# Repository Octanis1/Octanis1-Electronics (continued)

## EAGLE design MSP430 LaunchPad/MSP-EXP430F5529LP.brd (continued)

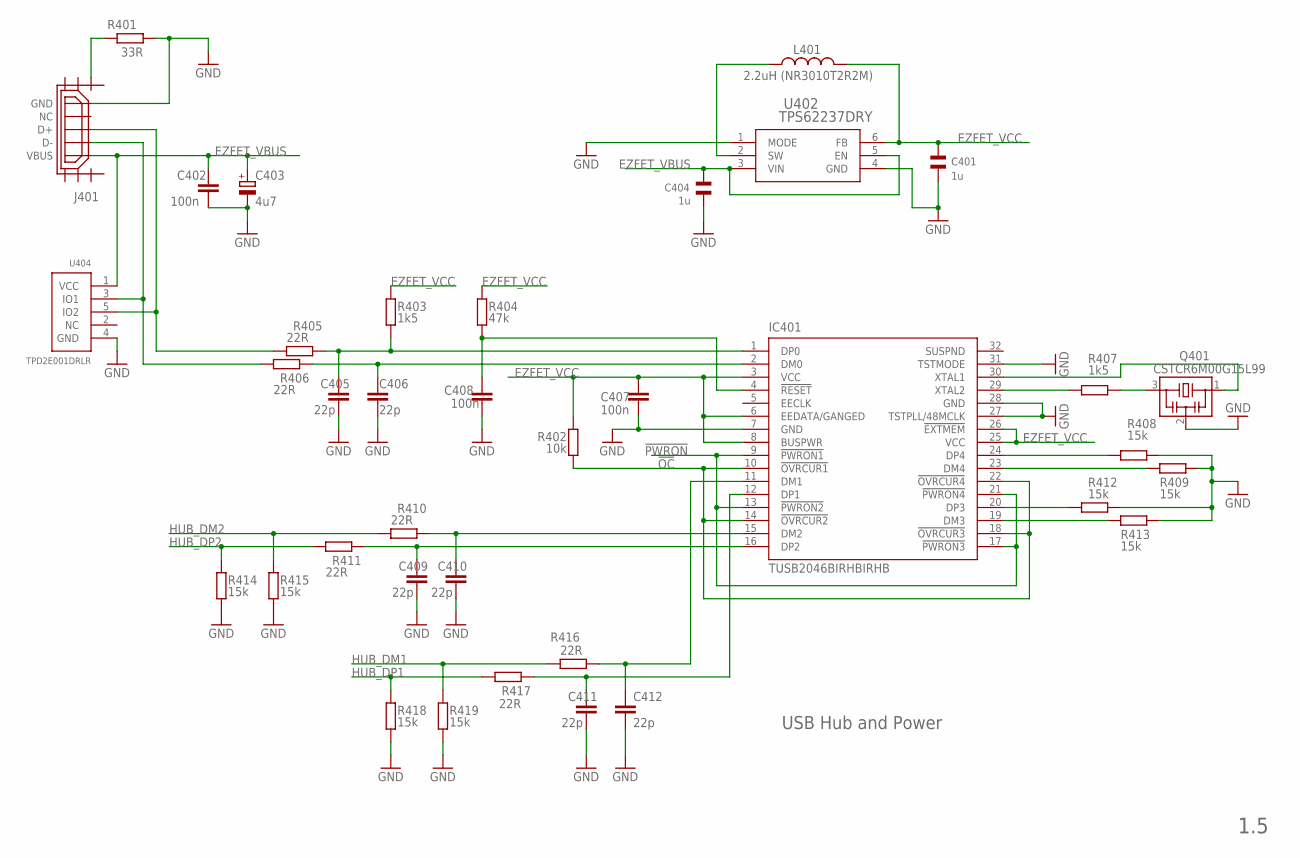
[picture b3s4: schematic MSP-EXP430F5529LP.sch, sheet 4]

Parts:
C401, C404: 1u; CSMD0805
C402, C407, C408: 100n; C0402
C403: 4u7; A/3216-18R
C405, C406, C409, C410, C411, C412: 22p; C0402
IC401: TUSB2046BIRHBIRHB; RHB_S-PQFP-N32
J401: USB_MICRO_FLIPPED; HIROSE-ZX62R-B-5P
L401: 2.2uH (NR3010T2R2M); L-NR3010
Q401: CSTCR6M00G15L99; MURATA-FILTER_CSTCR
R401: 33R; R0402
R402: 10k; R0402
R403, R407: 1k5; R0402
R404: 47k; R0402
R405, R406, R410, R411, R416, R417: 22R; R0402
R408, R409, R412, R413, R414, R415, R418, R419: 15k; R0402
U402: TPS62237DRY; DRY6
U404: TPD2E001DRLR; TPD2E001-DRL

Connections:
!OC: IC401.10 (!OVRCUR1), IC401.14 (!OVRCUR2), IC401.18 (!OVRCUR3), IC401.22 (!OVRCUR4), R402.2
!PWRON: IC401.9 (!PWRON1), IC401.13 (!PWRON2), IC401.17 (!PWRON3), IC401.21 (!PWRON4)
EZFET_VBUS: C402.1, C403.+, C404.2, J401.VBUS, U402.3 (VIN), U402.5 (EN), U404.1 (VCC); also elsewhere on the board
EZFET_VCC: C401.2, C407.1, IC401.3 (VCC), IC401.6 (EEDATA/GANGED), IC401.8 (BUSPWR), IC401.25 (VCC), IC401.26 (!EXTMEM), L401.P$2 (2), R402.1, R403.1, R404.1, U402.6 (FB); also elsewhere on the board
GND: C401.1, C402.2, C403.-, C404.1, C405.2, C406.2, C407.2, C408.2, C409.2, C410.2, C411.2, C412.2, IC401.7 (GND), IC401.27 (TSTPLL/48MCLK), IC401.28 (GND), IC401.31 (TSTMODE), J401.GND, Q401.2, R401.2, R408.1, R409.1, R412.1, R413.1, R414.2, R415.2, R418.2, R419.2, U402.1 (MODE), U402.4 (GND), U404.4 (GND); also elsewhere on the board
HUB_DM1: R416.2, R419.1; also elsewhere on the board
HUB_DM2: R410.2, R415.1; also elsewhere on the board
HUB_DP1: R417.2, R418.1; also elsewhere on the board
HUB_DP2: R411.2, R414.1; also elsewhere on the board
unnamed: C410.1, IC401.15 (DM2), R410.1
unnamed: C405.1, IC401.1 (DP0), R403.2, R405.1
unnamed: IC401.30 (XTAL1), Q401.1
unnamed: J401.SHIELD1, R401.1
unnamed: C406.1, IC401.2 (DM0), R406.1
unnamed: J401.D+, R405.2, U404.5 (IO2)
unnamed: J401.D-, R406.2, U404.3 (IO1)
unnamed: L401.P$1 (1), U402.2 (SW)
unnamed: IC401.29 (XTAL2), R407.2
unnamed: C412.1, IC401.11 (DM1), R416.1
unnamed: C411.1, IC401.12 (DP1), R417.1
unnamed: C409.1, IC401.16 (DP2), R411.1
unnamed: C408.1, IC401.4 (!RESET), R404.2
unnamed: IC401.20 (DP3), R412.2
unnamed: IC401.24 (DP4), R408.2
unnamed: IC401.23 (DM4), R409.2
unnamed: IC401.19 (DM3), R413.2
unnamed: Q401.3, R407.1

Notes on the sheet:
USB Hub and Power
1.5

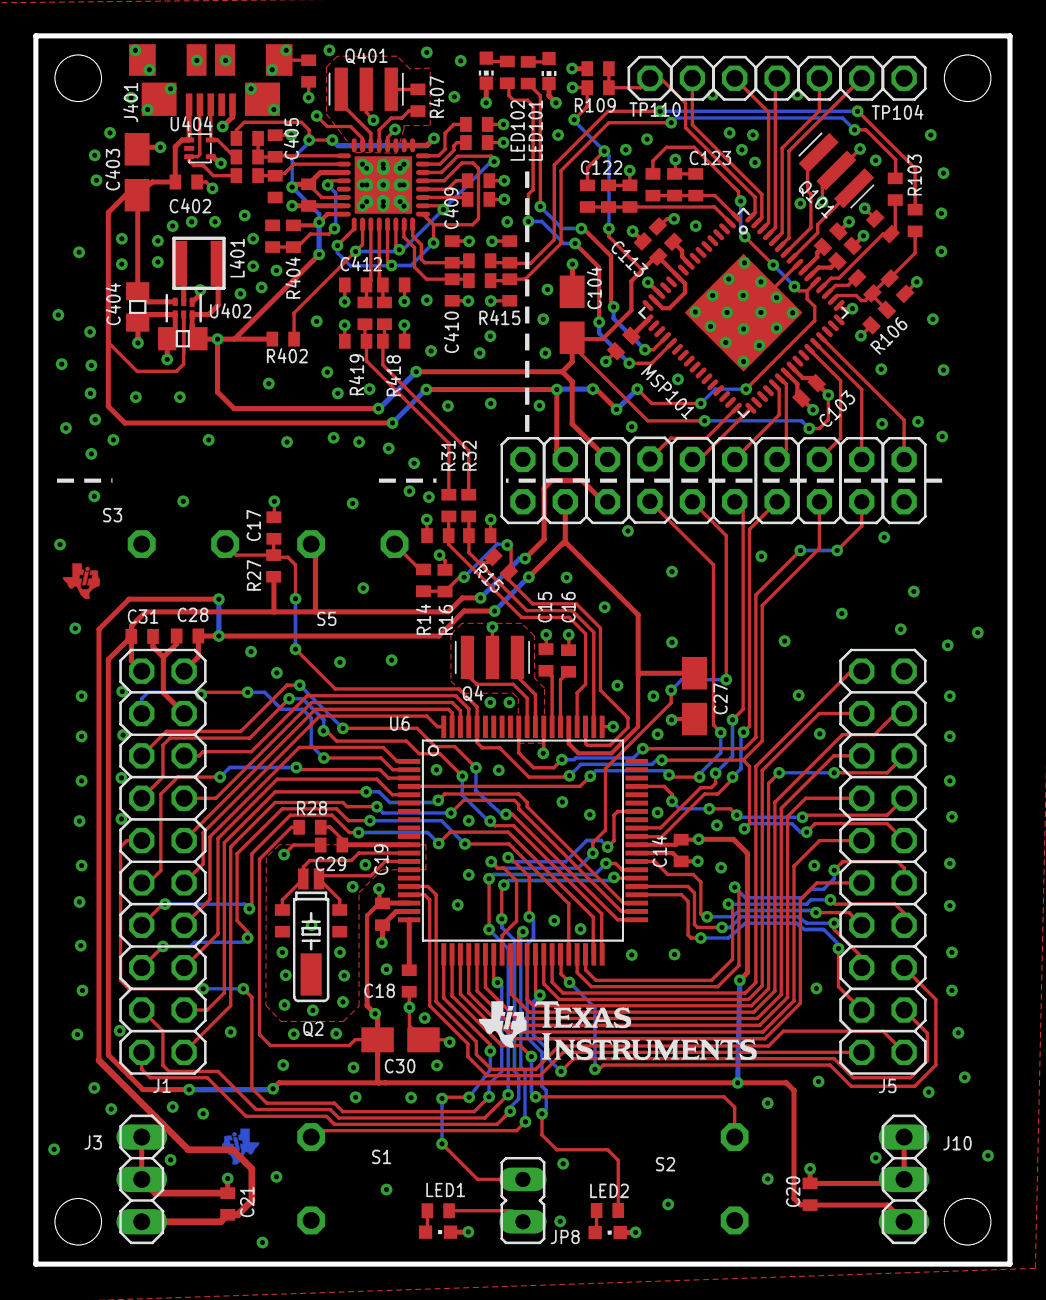
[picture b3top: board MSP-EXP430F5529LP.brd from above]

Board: 2 copper layers, 58.4 x 73.7 mm, 132 parts (1 on the bottom side), 117 nets.

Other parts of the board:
DRAW2: LOGO-ROCKET-10X7MM-BRD
U$1: LOGO16_TPLACE
U$2, U$5: TILOGO_SMALL

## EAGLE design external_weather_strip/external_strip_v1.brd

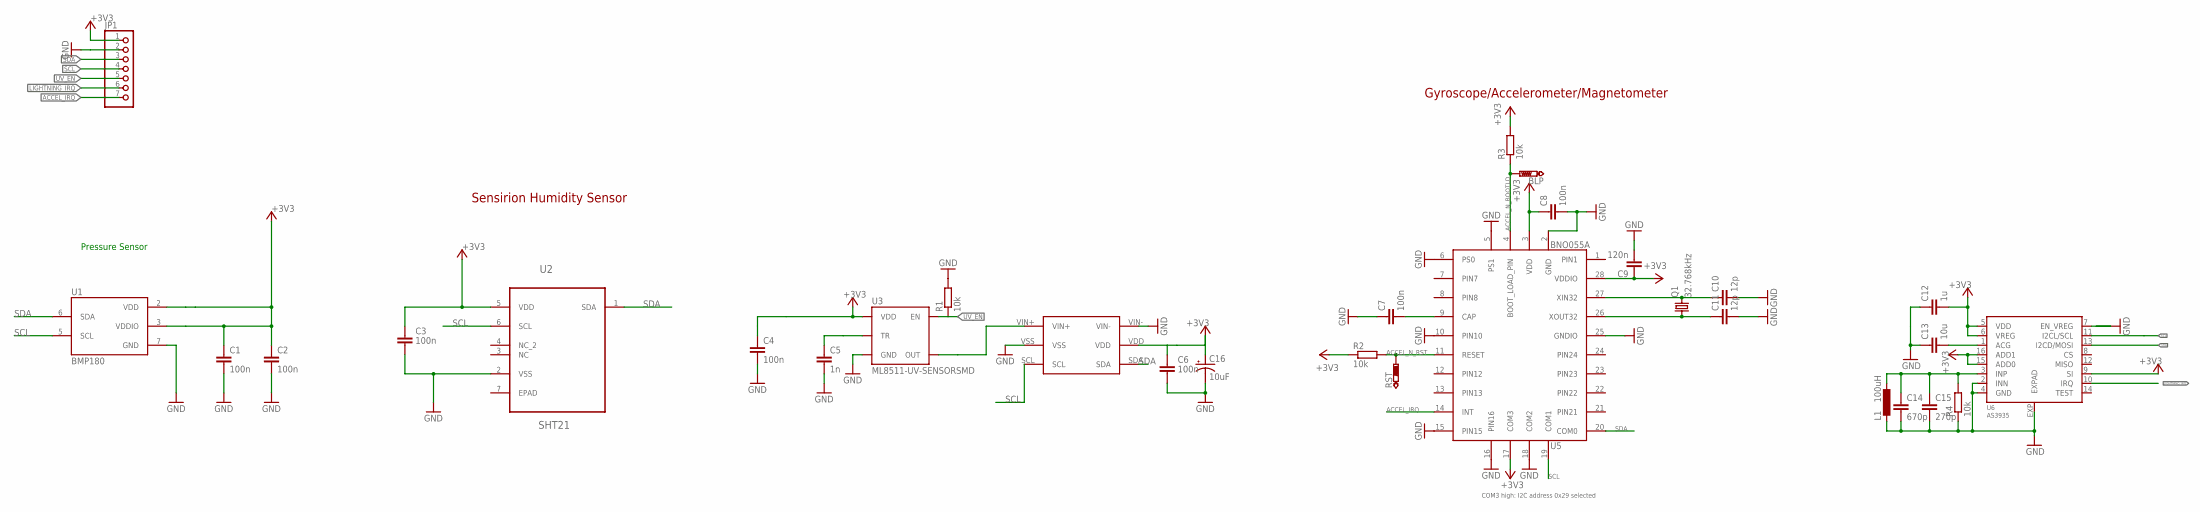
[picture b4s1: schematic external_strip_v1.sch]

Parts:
BLP: PTR1B1,27; B1,27
C1, C2, C3, C6, C7, C8: 100n; C0603
C4: 100n; 0603-CAP
C5: 1n; 0603-CAP
C9: 120n; C0603
C10, C11: 12p; C0603
C12: 1u; C0603
C13: 10u; C0603
C14: 670p; C0603
C15: 270p; C0603
C16: 10uF; EIA3216
JP1: PINHD-1X7; 1X07
L1: 100uH; COILCRAFT
Q1: 32.768kHz; FC-12M
R1, R2, R3, R4: 10k; R0603
RST: PTR1B1,27; B1,27
U1: BMP180
U2: SHT21; DFN300X300X110-7N
U3: ML8511-UV-SENSORSMD; ML8511
U4: MCP3425; SOT-23-6
U5: BNO055A; BNO055
U6: AS3935; 16LDMLPQ

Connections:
+3V3: C1.1, C2.1, C3.1, C4.1, C6.1, C8.1, C9.1, C12.2, C16.A (+), JP1.1, R2.1, R3.2, U1.2 (VDD), U1.3 (VDDIO), U2.5 (VDD), U3.7 (VDD), U4.VDD, U5.3 (VDD), U5.17 (COM3), U5.28 (VDDIO), U6.5 (VDD), U6.6 (VREG), U6.9 (SI), U6.15 (ADD0), U6.16 (ADD1)
ACCEL_IRQ: JP1.7, U5.14 (INT)
ACCEL_N_BOOTLD: BLP.TP, R3.1, U5.4 (BOOT_LOAD_PIN)
ACCEL_N_RST: R2.2, RST.TP, U5.11 (RESET)
GND: C1.2, C2.2, C3.2, C4.2, C5.2, C6.2, C7.1, C8.2, C9.2, C10.2, C11.2, C12.1, C13.1, C14.2, C15.2, C16.C (-), JP1.2, L1.2, R1.2, R4.1, U1.7 (GND), U2.2 (VSS), U3.5 (GND), U4.VIN-, U4.VSS, U5.2 (GND), U5.5 (PS1), U5.6 (PS0), U5.10 (PIN10), U5.15 (PIN15), U5.16 (PIN16), U5.18 (COM2), U5.25 (GNDIO), U6.2 (INN), U6.4 (GND), U6.7 (EN_VREG), U6.EXP (EXPAD)
LIGHTNING_IRQ: JP1.6, U6.10 (IRQ)
unnamed: U3.8 (OUT), U4.VIN+
unnamed: C13.2, U6.1 (ACG)
unnamed: C5.1, U3.10 (TR)
unnamed: C14.1, C15.1, L1.1, R4.2, U6.3 (INP)
unnamed: C7.2, U5.9 (CAP)
unnamed: C10.1, Q1.2, U5.27 (XIN32)
unnamed: C11.1, Q1.1, U5.26 (XOUT32)
SCL: JP1.4, U1.5 (SCL), U2.6 (SCL), U4.SCL, U5.19 (COM1), U6.11 (I2CL/SCL)
SDA: JP1.3, U1.6 (SDA), U2.1 (SDA), U4.SDA, U5.20 (COM0), U6.13 (I2CD/MOSI)
UV_EN: JP1.5, R1.1, U3.4 (EN)

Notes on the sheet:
Sensirion Humidity Sensor
Pressure Sensor
Gyroscope/Accelerometer/Magnetometer
COM3 high: I2C address 0x29 selected

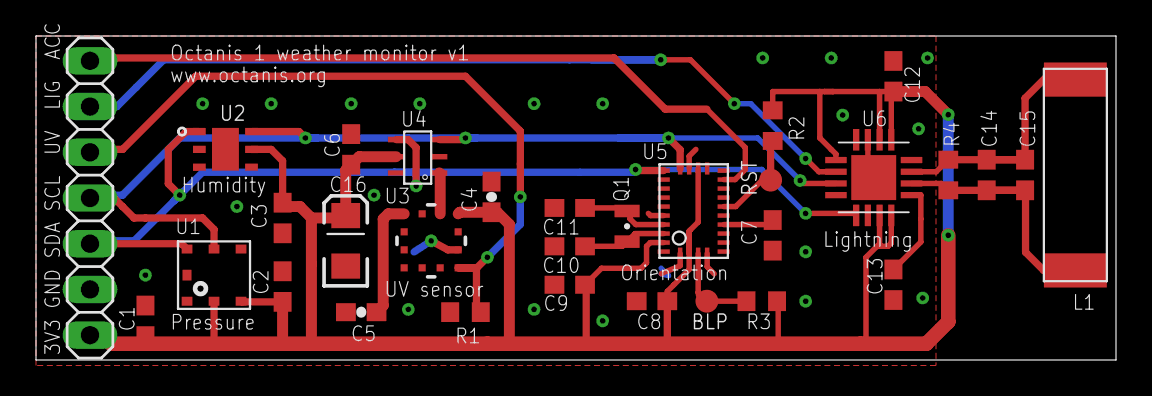
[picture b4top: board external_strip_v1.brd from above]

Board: 2 copper layers, 60.0 x 18.0 mm, 31 parts (0 on the bottom side), 16 nets.

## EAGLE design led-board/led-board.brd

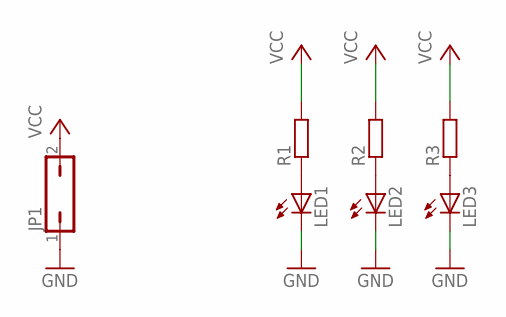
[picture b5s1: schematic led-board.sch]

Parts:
JP1: JP1Q; JP1
LED1, LED2, LED3: LED5MM
R1, R2, R3: R-EU_0414/15; 0414/15

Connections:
GND: JP1.1, LED1.K (C), LED2.K (C), LED3.K (C)
unnamed: LED1.A, R1.1
unnamed: LED2.A, R2.1
unnamed: LED3.A, R3.1
VCC: JP1.2, R1.2, R2.2, R3.2

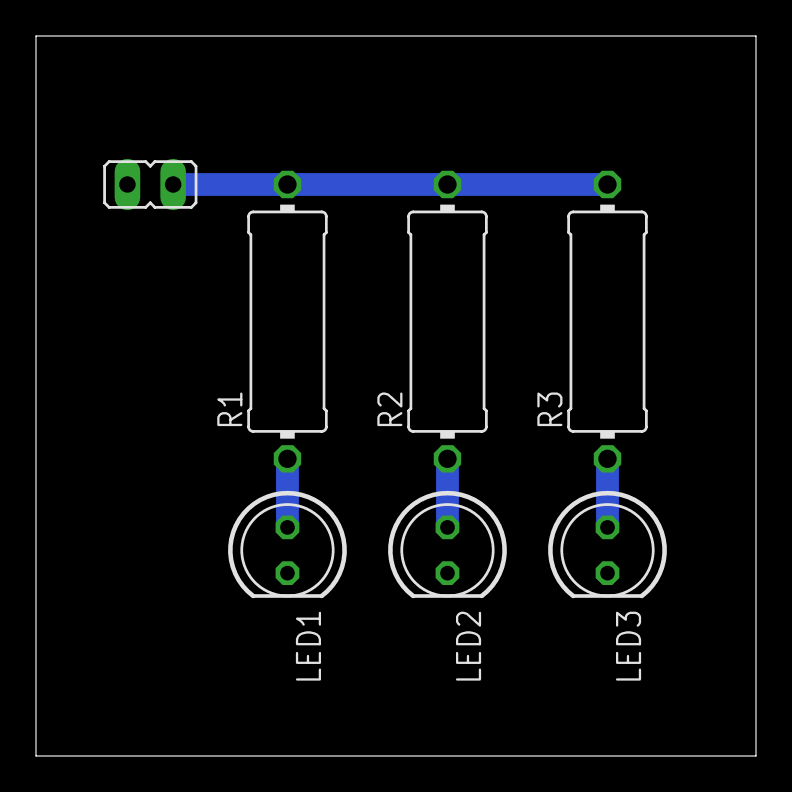
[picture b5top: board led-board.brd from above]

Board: 2 copper layers, 40.0 x 40.0 mm, 7 parts (0 on the bottom side), 5 nets.

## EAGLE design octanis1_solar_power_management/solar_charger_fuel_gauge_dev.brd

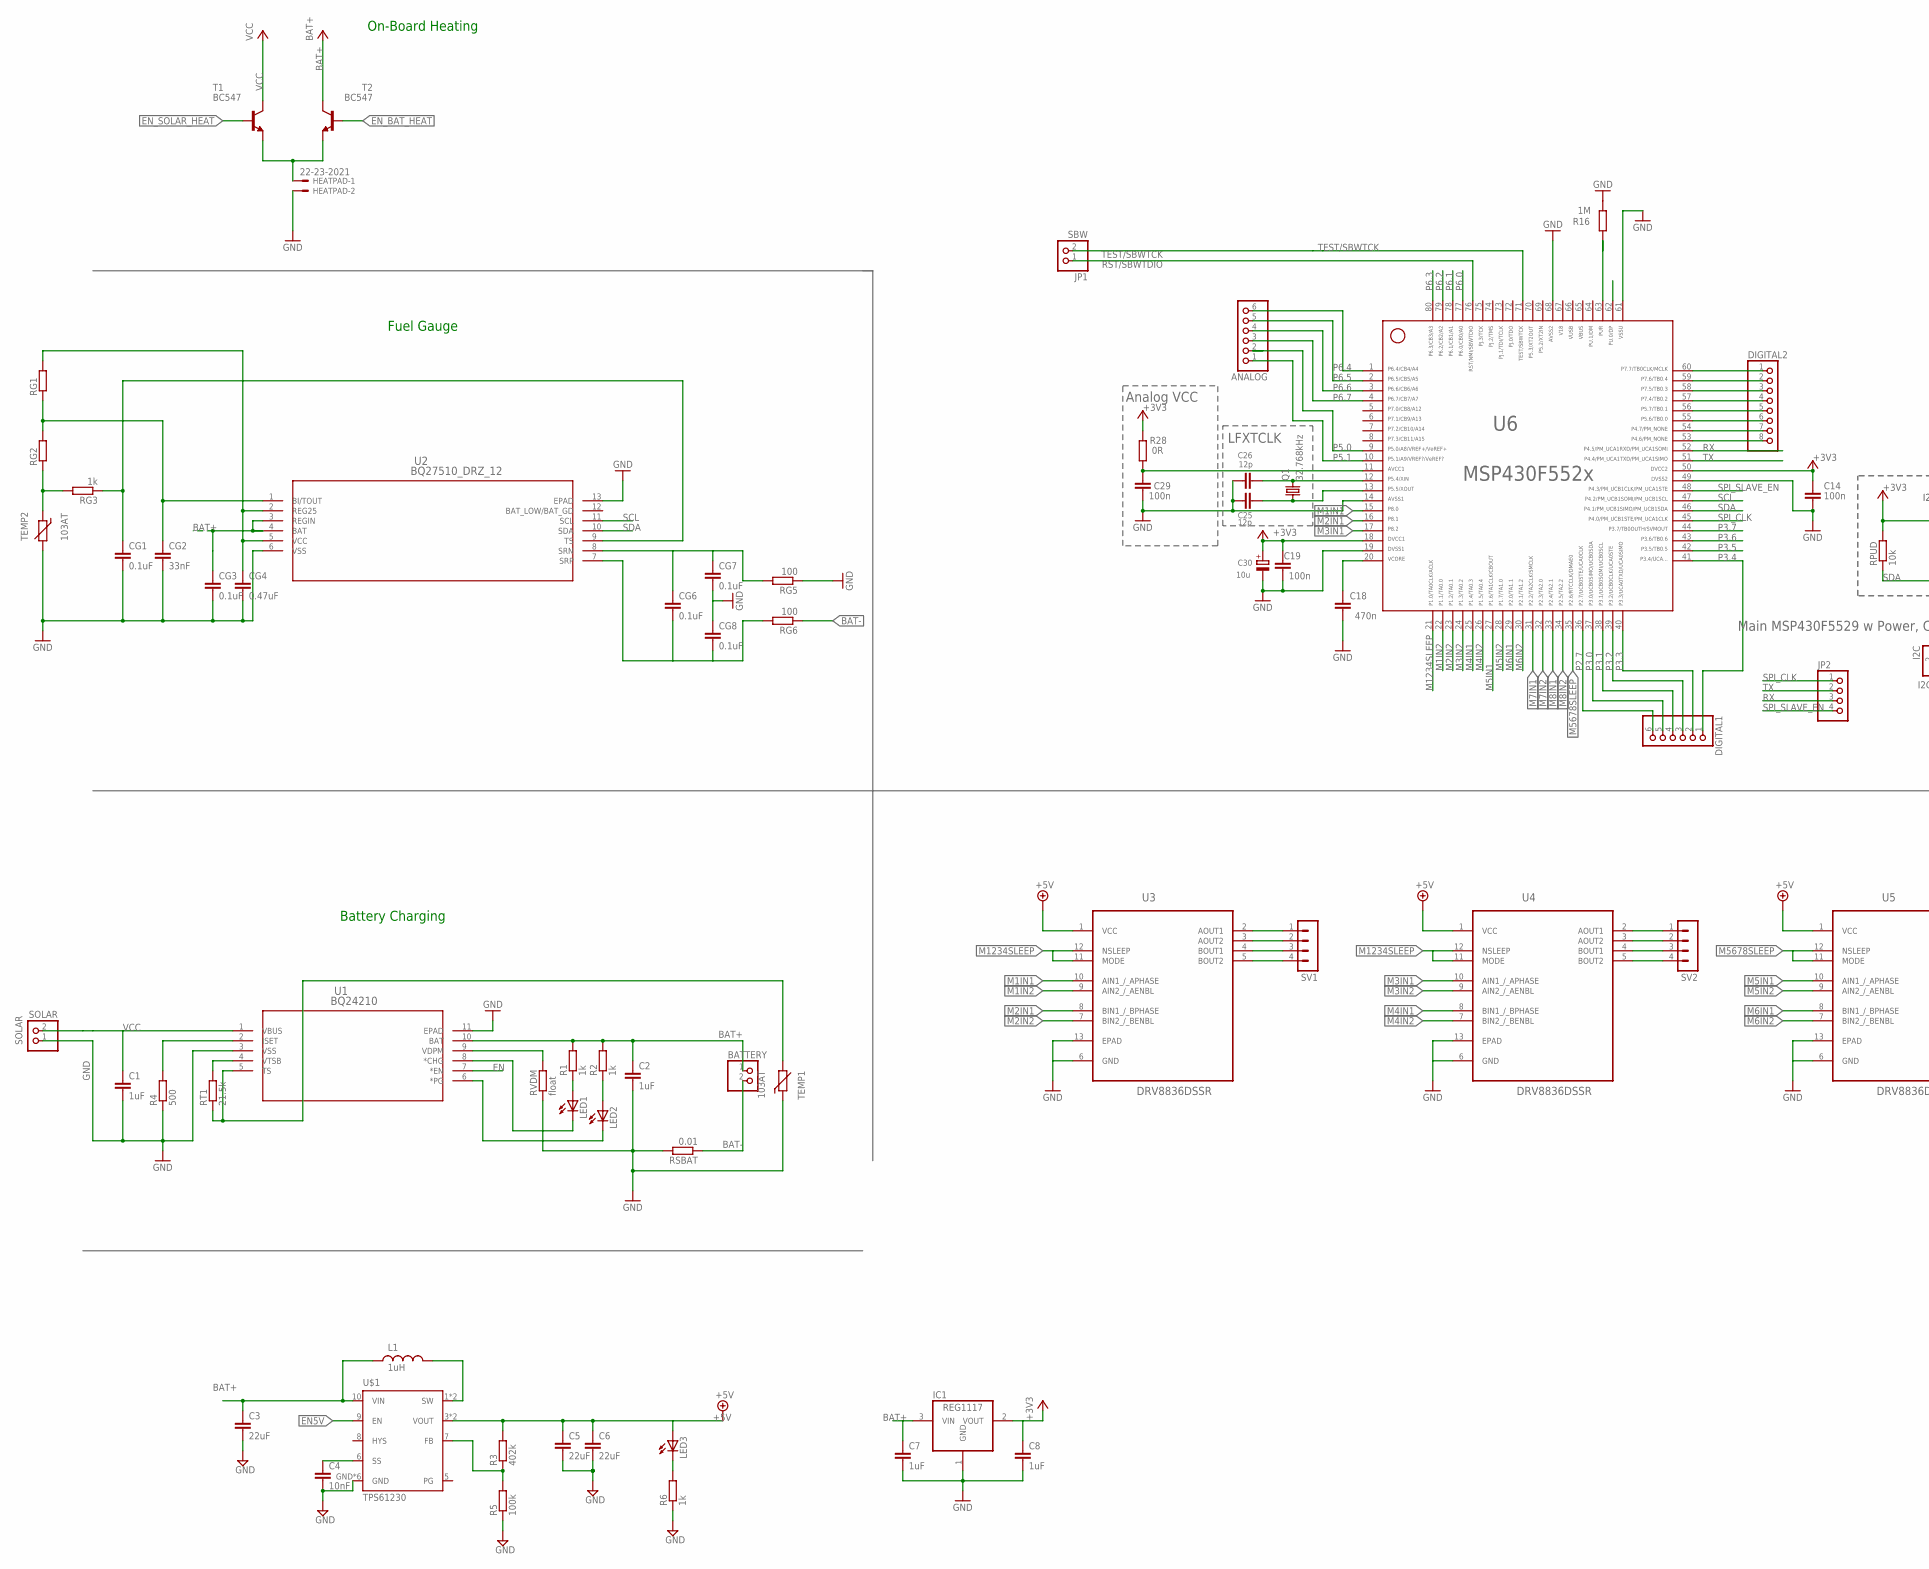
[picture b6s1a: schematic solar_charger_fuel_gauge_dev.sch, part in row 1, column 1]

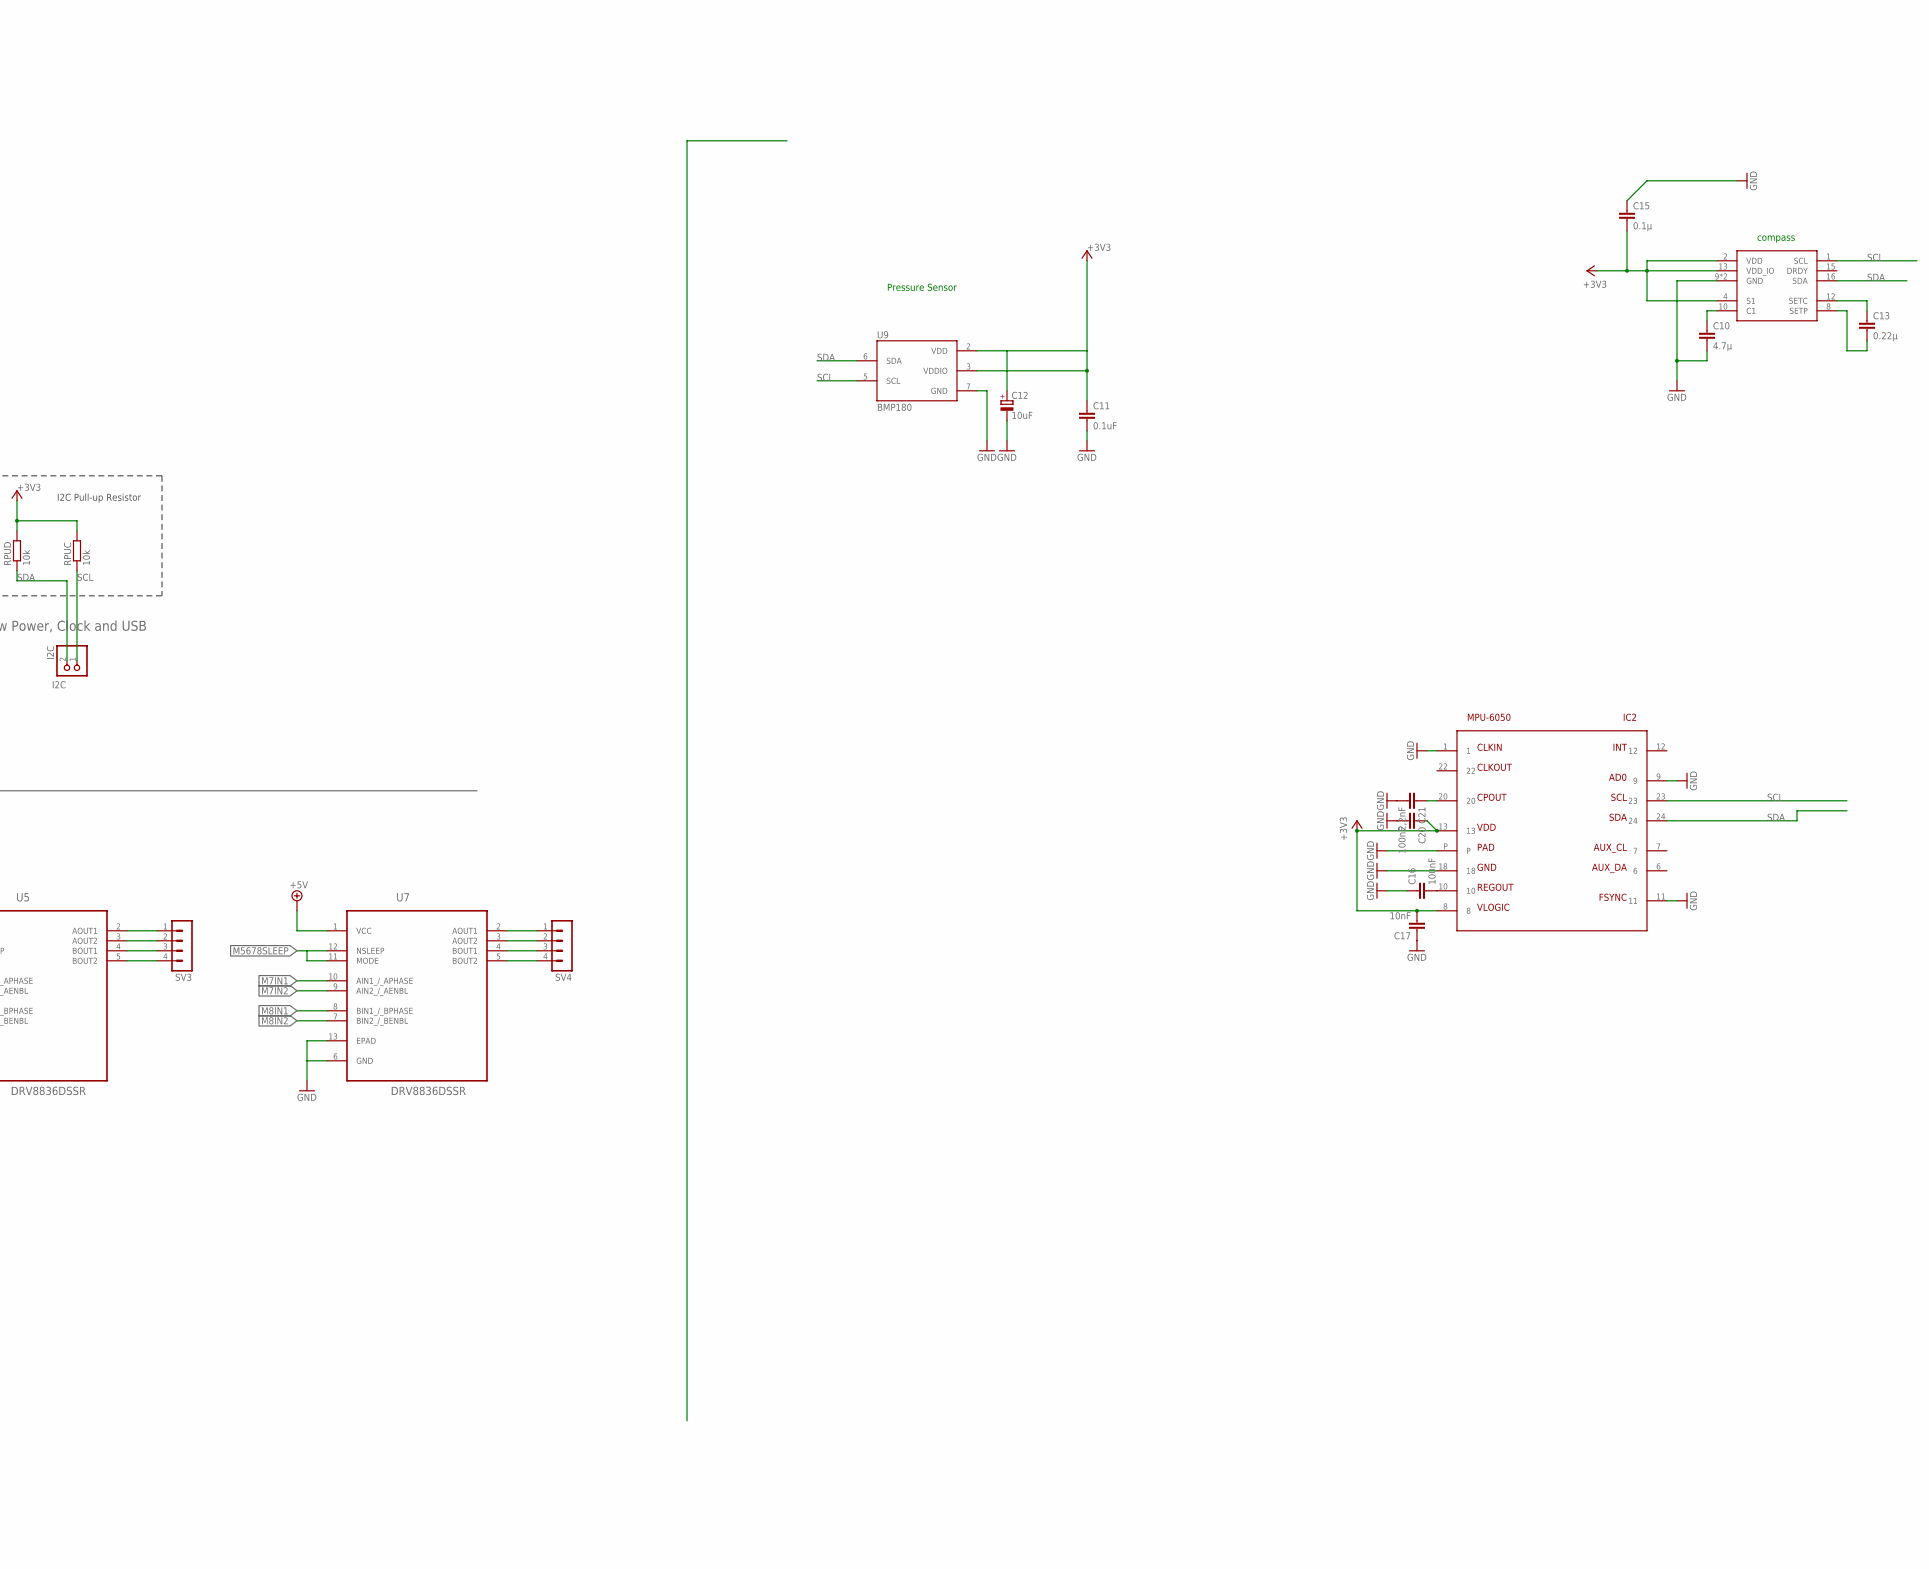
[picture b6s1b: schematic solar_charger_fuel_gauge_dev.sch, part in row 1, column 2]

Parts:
ANALOG: PINHD-1X6; 1X06
BATTERY: PINHD-1X2; 1X02
C1, C2: 1uF; C1206
C3, C5, C6: 22uF; C0603
C4, C17: 10nF; C0603
C7, C8: 1uF; C0603
C10: 4.7µ; C0603
C11: 0.1uF; C0603
C12: 10uF; A/3216-18R
C13: 0.22µ; C0603
C14, C19, C29: 100n; C0603
C15: 0.1µ; C0603
C16, C20: 100nF; C0603
C18: 470n; C0603
C21: 2,2nF; C0603
C25, C26: 12p; C0603
C30: 10u; A/3216-18R
CG1, CG3, CG6, CG7, CG8: 0.1uF; C0603
CG2: 33nF; C0603
CG4: 0.47uF; C0603
COMPASS: HMC5883L; LPCC16
DIGITAL1: PINHD-1X6; 1X06
DIGITAL2: PINHD-1X8; 1X08
HEATPAD: 22-23-2021
I2C: I2C; 1X02
IC1: REG1117; SOT223
IC2: MPU-6050; QFN24
JP1: SBW; 1X02
JP2: PINHD-1X4; 1X04
L1: 1uH; XFL4020
LED1, LED2: LEDCHIP-LED0603; CHIP-LED0603
LED3: LEDCHIPLED_0603; CHIPLED_0603
Q1: 32.768kHz; FC-12M
R1, R2, R6: 1k; R0603
R3: 402k; R0603
R4: 500; R1206
R5: 100k; R0603
R16: 1M; R0603
R28: 0R; R0603
RG1, RG2: R-EU_R0603; R0603
RG3: 1k; R0603
RG5, RG6: 100; R0603
RPUC: 10k; R0603
RPUD: 10k; R0603
RSBAT: 0.01; R1206
RT1: 21.5k; R1206
RVDM: float; R1206
SOLAR: SOLAR; 1X02
SV1, SV2, SV3, SV4: MA04-1
T1, T2: BC547; TO92
TEMP1, TEMP2: 103AT; RS-2,5
U1: BQ24210; DQC10_P84X2P4
U2: BQ27510_DRZ_12; DRZ12_1P95X2P45
U3, U4, U5, U7: DRV8836DSSR; SON50P200X300X80-13N
U6: MSP430F5529IPNR; PN80
U9: BMP180
U$1: TPS61230; DRC-S-PVSON-N11

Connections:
65: U6.65
66: U6.66
67: U6.67
+3V3: C8.1, C11.1, C12.+, C14.1, C15.2, C17.2, C19.2, C20.1, C30.+, COMPASS.2 (VDD), COMPASS.4 (S1), COMPASS.13 (VDD_IO), IC1.2 (VOUT), IC2.8, IC2.13, R28.2, RPUC.2, RPUD.2, U6.18, U6.50, U9.2 (VDD), U9.3 (VDDIO)
+5V: C5.1, C6.1, LED3.A, R3.2, U3.1 (VCC), U4.1 (VCC), U5.1 (VCC), U7.1 (VCC), U$1.3 (VOUT), U$1.4 (VOUT)
AVCC: C29.1, R28.1, U6.11
BAT+: BATTERY.1, C2.1, C3.1, C7.1, CG3.1, IC1.3 (VIN), L1.P$1 (1), R1.2, R2.2, T2.3 (C), U1.10 (BAT), U2.3 (REGIN), U2.4 (BAT), U$1.10 (VIN)
BAT-: BATTERY.2, RG6.1, RSBAT.1
EN: U1.7 (*EN)
EN5V: U$1.9 (EN)
EN_BAT_HEAT: T2.2 (B)
EN_SOLAR_HEAT: T1.2 (B)
GND: C1.2, C2.2, C3.2, C4.2, C5.2, C6.2, C7.2, C8.2, C10.2, C11.2, C12.-, C14.2, C15.1, C16.1, C17.1, C18.1, C19.1, C20.2, C21.2, C25.1, C26.1, C29.2, C30.-, CG1.2, CG2.2, CG3.2, CG4.2, CG7.2, CG8.1, COMPASS.9 (GND), COMPASS.11 (GND), HEATPAD.2, IC1.1 (GND), IC2.1, IC2.9, IC2.11, IC2.18, IC2.P, R4.1, R5.1, R6.1, R16.1, RG5.1, RSBAT.2, RVDM.1, SOLAR.1, TEMP1.1, TEMP2.2, U1.3 (VSS), U1.11 (EPAD), U2.6 (VSS), U2.13 (EPAD), U3.6 (GND), U3.13 (EPAD), U4.6 (GND), U4.13 (EPAD), U5.6 (GND), U5.13 (EPAD), U6.14, U6.19, U6.49, U6.61, U6.68, U7.6 (GND), U7.13 (EPAD), U9.7 (GND), U$1.GND, U$1.GND@1 (GND), U$1.GND@2 (GND), U$1.GND@3 (GND), U$1.GND@4 (GND), U$1.GND@5 (GND)
IND: L1.P$2 (2), U$1.1 (SW), U$1.2 (SW)
M1IN1: U3.10 (AIN1_/_APHASE), U6.15
M1IN2: U3.9 (AIN2_/_AENBL), U6.22
M2IN1: U3.8 (BIN1_/_BPHASE), U6.16
M2IN2: U3.7 (BIN2_/_BENBL), U6.23
M3IN1: U4.10 (AIN1_/_APHASE), U6.17
M3IN2: U4.9 (AIN2_/_AENBL), U6.24
M4IN1: U4.8 (BIN1_/_BPHASE), U6.25
M4IN2: U4.7 (BIN2_/_BENBL), U6.26
M5IN1: U5.10 (AIN1_/_APHASE), U6.27
M5IN2: U5.9 (AIN2_/_AENBL), U6.28
M6IN1: U5.8 (BIN1_/_BPHASE), U6.29
M6IN2: U5.7 (BIN2_/_BENBL), U6.30
M7IN1: U6.31, U7.10 (AIN1_/_APHASE)
M7IN2: U6.32, U7.9 (AIN2_/_AENBL)
M8IN1: U6.33, U7.8 (BIN1_/_BPHASE)
M8IN2: U6.34, U7.7 (BIN2_/_BENBL)
M1234SLEEP: U3.11 (MODE), U3.12 (NSLEEP), U4.11 (MODE), U4.12 (NSLEEP), U6.21
M5678SLEEP: U5.11 (MODE), U5.12 (NSLEEP), U6.35, U7.11 (MODE), U7.12 (NSLEEP)
unnamed: CG2.1, RG1.1, RG2.2, U2.1 (BI/TOUT)
unnamed: LED1.A, R1.1
unnamed: LED2.A, R2.1
unnamed: LED1.C, U1.8 (*CHG)
unnamed: LED2.C, U1.6 (*PG)
unnamed: RVDM.2, U1.9 (VDPM)
unnamed: RT1.1, TEMP1.2, U1.5 (TS)
unnamed: RT1.2, U1.4 (VTSB)
unnamed: R4.2, U1.2 (ISET)
unnamed: SV2.1, U4.2 (AOUT1)
unnamed: DIGITAL2.1, U6.60
unnamed: DIGITAL2.2, U6.59
unnamed: C10.1, COMPASS.10 (C1)
unnamed: C16.2, IC2.10
unnamed: C21.1, IC2.20
unnamed: DIGITAL2.3, U6.58
unnamed: DIGITAL2.4, U6.57
unnamed: DIGITAL2.5, U6.56
unnamed: DIGITAL2.6, U6.55
unnamed: DIGITAL2.7, U6.54
unnamed: C13.2, COMPASS.8 (SETP)
unnamed: DIGITAL2.8, U6.53
unnamed: C13.1, COMPASS.12 (SETC)
unnamed: RG2.1, RG3.2, TEMP2.1
unnamed: CG1.1, RG3.1, U2.9 (TS)
unnamed: CG4.1, RG1.2, U2.2 (REG25), U2.5 (VCC)
unnamed: CG6.1, CG7.1, RG5.2, U2.8 (SRN)
unnamed: HEATPAD.1, T1.1 (E), T2.1 (E)
unnamed: CG6.2, CG8.2, RG6.2, U2.7 (SRP)
unnamed: SV2.2, U4.3 (AOUT2)
unnamed: SV2.3, U4.4 (BOUT1)
unnamed: SV2.4, U4.5 (BOUT2)
unnamed: C4.1, U$1.6 (SS)
unnamed: R3.1, R5.2, U$1.7 (FB)
unnamed: LED3.C, R6.2
unnamed: SV3.1, U5.2 (AOUT1)
unnamed: SV3.2, U5.3 (AOUT2)
unnamed: SV3.3, U5.4 (BOUT1)
unnamed: SV3.4, U5.5 (BOUT2)
unnamed: SV1.1, U3.2 (AOUT1)
unnamed: SV1.2, U3.3 (AOUT2)
unnamed: SV1.3, U3.4 (BOUT1)
unnamed: SV1.4, U3.5 (BOUT2)
unnamed: SV4.1, U7.2 (AOUT1)
unnamed: SV4.2, U7.3 (AOUT2)
unnamed: SV4.3, U7.4 (BOUT1)
unnamed: SV4.4, U7.5 (BOUT2)
P2.7: DIGITAL1.6, U6.36
P3.0: DIGITAL1.5, U6.37
P3.1: DIGITAL1.4, U6.38
P3.2: DIGITAL1.3, U6.39
P3.3: DIGITAL1.2, U6.40
P3.4: DIGITAL1.1, U6.41
P3.5: U6.42
P3.6: U6.43
P3.7: U6.44
P5.0: ANALOG.2, U6.9
P5.1: ANALOG.1, U6.10
P5.4/XIN: C26.2, Q1.2, U6.12
P5.5/XOUT: C25.2, Q1.1, U6.13
P6.0: U6.77
P6.1: U6.78
P6.2: U6.79
P6.3: U6.80
P6.4: ANALOG.6, U6.1
P6.5: ANALOG.5, U6.2
P6.6: ANALOG.4, U6.3
P6.7: ANALOG.3, U6.4
PG: U$1.5 (PG)
RST/SBWTDIO: JP1.1, U6.76
RX: JP2.3, U6.52
SCL: COMPASS.1 (SCL), I2C.1, IC2.23, RPUC.1, U2.11 (SCL), U6.47, U9.5 (SCL)
SDA: COMPASS.16 (SDA), I2C.2, IC2.24, RPUD.1, U2.10 (SDA), U6.46, U9.6 (SDA)
SPI_CLK: JP2.1, U6.45
SPI_SLAVE_EN: JP2.4, U6.48
TARGET_DP: U6.62
TARGET_PUR: R16.2, U6.63
TEST/SBWTCK: JP1.2, U6.71
TX: JP2.2, U6.51
VCC: C1.1, SOLAR.2, T1.3 (C), U1.1 (VBUS)
VCORE: C18.2, U6.20

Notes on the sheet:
Battery Charging
Fuel Gauge
LFXTCLK
Main MSP430F5529 w Power, Clock and USB
Analog VCC
I2C Pull-up Resistor
On-Board Heating
Pressure Sensor
compass

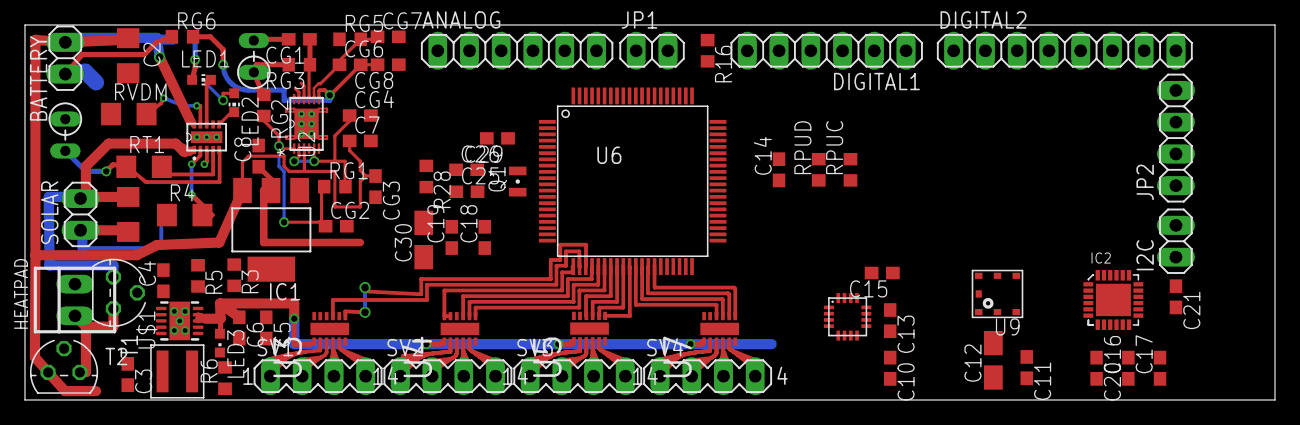
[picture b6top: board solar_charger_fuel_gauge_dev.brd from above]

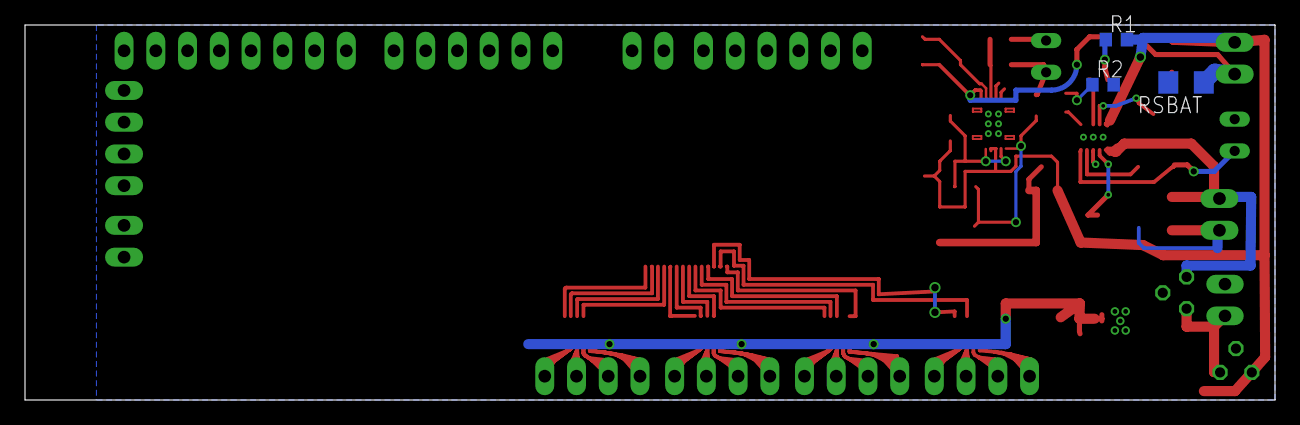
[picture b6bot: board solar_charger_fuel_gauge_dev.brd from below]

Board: 4 copper layers, 100.0 x 30.0 mm, 83 parts (3 on the bottom side), 97 nets.
